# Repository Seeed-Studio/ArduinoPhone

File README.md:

Arduino Phone
---------------------------------------------------------

Combining Arduino and other shield modules, we make a mobile phone named Arduino Phone. Meanwhile, we printed a shell for it with the 3D printer. Although it’s not such fine as you think, even a little bit clunky, it’s still very cool. That is the point this is a cell phone made by ourselves.

<br>
### Usage:

This is a Sketchbook of Arduino.([How to use Sketchbook](http://www.seeedstudio.com/wiki/How_To_Use_Sketchbook "How to use Sketchbook"))

This Sketchbook includes a Phone demo and some libraries that included. 

We had an instructable about how to make an Arduino Phone, for more information, please refer to [Arduino Phone Instructable](http://www.instructables.com/id/ArduinoPhone/)

### TFT Shield version

The default TFT version is TFT Touch Shield V2, if you want to work with TFT v1, there's few to be modify in the code.

1. Line 34, 35 of Demo.ino
2. Line 38, 39 of UI_ArduinoPhone.cpp
3. Line 32 of UI_ArduinoPhone_dfs.h

<br>
----

This software is written by loovee ([luweicong@seeedstudio.com](luweicong@seeedstudio.com)) for seeed studio<br>
and is licensed under [The MIT License](http://opensource.org/licenses/mit-license.php). Check License.txt for more information.<br>

Contributing to this software is warmly welcomed. You can do this basically by<br>
[forking](https://help.github.com/articles/fork-a-repo), committing modifications and then [pulling requests](https://help.github.com/articles/using-pull-requests) (follow the links above<br>
for operating guide). Adding change log and your contact into file header is encouraged.<br>
Thanks for your contribution.

Seeed Studio is an open hardware facilitation company based in Shenzhen, China. <br>
Benefiting from local manufacture power and convenient global logistic system, <br>
we integrate resources to serve new era of innovation. Seeed also works with <br>
global distributors and partners to push open hardware movement.<br>

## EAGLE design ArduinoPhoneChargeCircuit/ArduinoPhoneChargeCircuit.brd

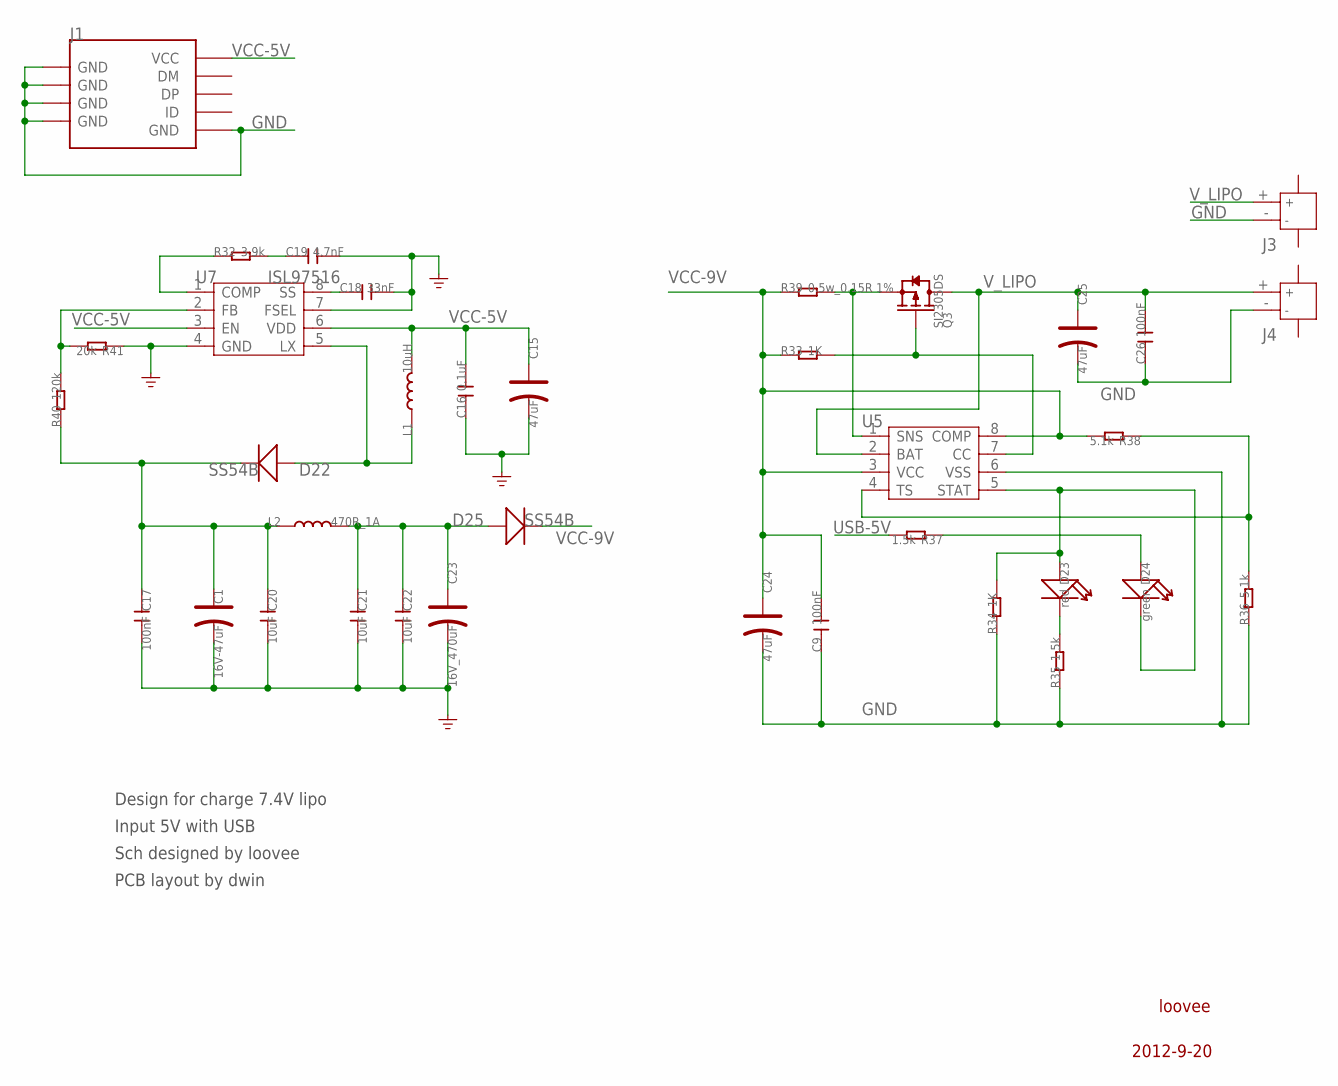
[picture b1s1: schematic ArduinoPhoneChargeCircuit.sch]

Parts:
C1: 16V-47uF; AVX-C
C9, C26: 100nF; 0805
C15: 47uF; 1210
C16: 0.1uF; 0603
C17: 100nF; 0603
C18: 33nF; 0603
C19: 4.7nF; 0603
C20, C21, C22: 10uF; 0805
C23: 16V_470uF; AVX-E
C24: 47uF; AVX-C
C25: 47uF; AVX-A
D22, D25: SS54B; SMB
D23: red; LED-2P-2.54-3MM
D24: green; LED-2P-2.54-3MM
J1: USB-MINIUSB-5P-STRONG; MINI-SMD-5P
J3, J4: JACK-JST-2P-SMD-PW'2.0'; JST-SMD-2.0-90D
L1: 10uH; 2626
L2: 470R_1A; L0805
Q3: SI2305DS; SOT23
R32: 3.9k; R0603
R33, R34: 1K; R0805
R35, R37: 1.5k; R0805
R36, R38: 5.1k; R0805
R39: 0.5w_0.15R 1%; R2512
R40: 120k; R0603
R41: 20k; R0603
U5: BQ2057WPW; TSSOP8
U7: ISL97516; MSOP8

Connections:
GND: C1.-, C9.1, C15.-, C16.1, C17.2, C18.2, C19.2, C20.2, C21.2, C22.2, C23.-, C24.-, C25.-, C26.1, J1.5 (GND), J1.GND@1 (GND), J1.GND@2 (GND), J1.GND@3 (GND), J1.GND@4 (GND), J3.- (2), J4.- (2), R34.1, R35.1, R36.1, R41.1, U5.6 (VSS), U7.4 (GND), U7.7 (FSEL)
unnamed: Q3.2 (S), R39.2, U5.1 (SNS)
unnamed: Q3.1 (G), R33.2, U5.7 (CC)
unnamed: D23.K (-), R35.2
unnamed: R36.2, R38.1, U5.4 (TS)
unnamed: D23.A (+), D24.K (-), R34.2, U5.5 (STAT)
unnamed: D24.A (+), R37.1
unnamed: C18.1, U7.8 (SS)
unnamed: R40.2, R41.2, U7.2 (FB)
unnamed: D22.+, L1.1, U7.5 (LX)
unnamed: R32.1, U7.1 (COMP)
unnamed: C19.1, R32.2
OUTPUT: C1.+, C17.1, C20.1, D22.-, L2.1, R40.1
OUTPUT2: C21.1, C22.1, C23.+, D25.+, L2.2
USB-5V: R37.2
VCC-5V: C15.+, C16.2, J1.1 (VCC), L1.2, U7.3 (EN), U7.6 (VDD)
VCC-9V: C9.2, C24.+, D25.-, R33.1, R38.2, R39.1, U5.3 (VCC), U5.8 (COMP)
V_LIPO: C25.+, C26.2, J3.+ (1), J4.+ (1), Q3.3 (D), U5.2 (BAT)

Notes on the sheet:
Design for charge 7.4V lipo
Input 5V with USB
Sch designed by loovee
PCB layout by dwin
loovee
2012-9-20

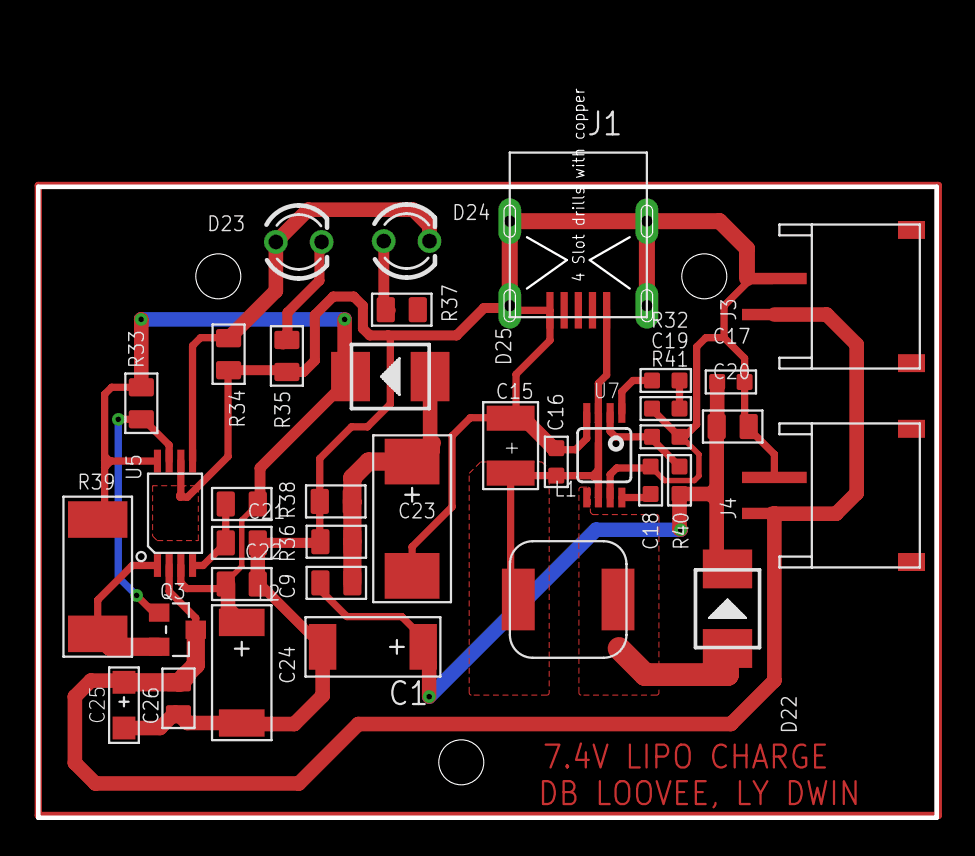
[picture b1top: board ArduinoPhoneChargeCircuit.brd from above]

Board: 2 copper layers, 49.9 x 43.3 mm, 36 parts (0 on the bottom side), 17 nets.

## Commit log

2013-04-16 Add all code, fit for TFT Shield 2.0
2013-04-16 change readme
2013-04-17 change ArduinoPhoneCode.ino to ArduinoPhone.ino
2013-04-17 no change, just for commit....
2013-04-17 try to debug a bug but with no luch to slove it
2013-04-17 use tft touch shield 1.0
2013-04-25 add libraries
2013-04-26 touch works with mega and leonardo
2013-07-17 ArduinoPhoneChargeCircuit added
2013-07-22 3D Shell stl file
2014-01-02 make it to a sketchbook
2014-01-02 read me
2014-01-02 license
2014-01-02 add name to readme
2015-10-21 Support TFT Touch Shield V2
2015-12-07 rename PhoneCode
2024-10-08 Add sync_issues GitHub Action for workflows
